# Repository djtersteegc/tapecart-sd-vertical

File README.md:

A respin of the [Tapuino](https://github.com/sweetlilmre/tapuino) hardware design for Kim Jorgensen's [Tapecart SD](https://github.com/KimJorgensen/tapecart) firmware that added SD support to Ingo Korb's original [Tapecart](https://github.com/ikorb/tapecart) project for the Commodore 64.  My three design goals for this were:

1. Full sized SD card slot.
2. Physically anchor the edge connector so insertion/removal forces don't stress the solder joints like some of the other designs.
3. SMD to make it as compact as possible, but keep the board single sided and using larger 0805 components with hand solder footprints to make it easy to build.

# Case

The case was created in DesignSpark and available in two different versions.  One with a finger pull handle for easy removal, and one without, but with grip ridges on the sides to aid in removal.  I find the Chinese Jamma/805 connectors from AliExpress to be extra tight on my Commodore's edge connectors, so the handle version is my preferred one.

There are a pair of light pipes that should be printed in transparent material, or you can just leave them off completely. The case is designed to be printed at 0.2mm layer heights and assembled with two M3x16mm screws through the connector body and two M3 nuts pushed into either the handle or lid.

# BOM

There's an interactive BOM [here](https://djtersteegc.github.io/tapecart-sd-vertical/ibom.html), and CSV version with footprint info [here](https://djtersteegc.github.io/tapecart-sd-vertical/bom.csv). The interactive one is super useful when placing the SMD comonents.

C5 is an optional bulk capacitor for the 5V power rail near the MCU.  In my experience building these it is not needed.

The LED's can either be driven directly from the ATmega328P, since they are only drawing ~10ma through the 330R resistors at R4 and R5, by bridging JP1 and JP2. You can also populate R2, R3, Q1, Q2 (leave JP1/2 open in this case) and drive them via a transistor like the original Tapuino design.

The SD card connector is commonly available from several different Chinese suppliers and often called "long body", "non popping", or "push pull" on AliExpress or eBay.

https://www.aliexpress.us/item/3256805779248826.html

Here's some links on LCSC.

https://www.lcsc.com/product-detail/SD-Card-Connectors_Hanbo-Electronic-SD-112_C961673.html

https://www.lcsc.com/product-detail/SD-Card-Connectors_XUNPU-SD-102_C266602.html

https://www.lcsc.com/product-detail/SD-Card-Connectors_Megastar-ZX-SD-282-8Y_C7419835.html

It should also cross with a Wurth 693063010911 or AMP GSD090012SEU if you want something domestically.

# Assembly

Assemble all the SMD components.  I use solder paste hand applied with pnematic dispenser and then finish on a hot plate.  But you can also hand solder, use hot air, or even order a stencil for paste application and use a proper reflow oven. I use a green LED for Read and Red for Write. Make sure to observe polarity with the green stripe on the LED to the right matching the white stripe on the PCB silkscreen.

Do NOT install the 2x3 ICSP pin header at J2.  I would recommend flashing the firmware at this point to do basic checks since it's easier to do board rework before you install the 805 connector.

To install the connector, you will want to print the case back first so it can be used a spacer between the connector and board.  Tighten the screws gently so you can still slide out the case in the future and then solder a couple pins to hold it.  Then slide out the case and do the rest.

When complete it should look something like this.

Press the light pipes into the two LED openings with the lip side facing up and then slide the board in. If you can't slide the PCB under the light pipes, they are installed upside down.  The side mounted LED's should keep the light pipes from falling out, even if they aren't a tight friction fit in the openings.

# Firmware Flashing

The ATmega328P is the same used an Arduino Uno/Nano/Micro, but lacks the necessary bootloader firmware and serial interfaces to flash via the Arduino IDE or programs like XLoader. You could program the chip before installing it with something like a [TL866/T48](TL866/T48) and a [TQFP32 to DIP 32 adapter](https://www.aliexpress.us/item/2251832227450089.html), but I prefer to just use a cheap [UBSASP](https://www.aliexpress.us/item/2251832600419163.html) and [avrdude](https://github.com/avrdudes/avrdude). Make sure you get a 10 pin to 8 pin adapter with the USBASP if it isn't natively an 8 pin model.

Since you didn't solder the 2x3 pin header on the ICSP port J2, you will need to hold the header pins at an angle in the holes to make contact while you run avrdude.  If you're feeling fancy, you could spring for a [2x3 double row 2.54mm test clip](https://www.aliexpress.us/item/3256805646654844.html) or [handheld pogo pin probe](https://www.aliexpress.us/item/3256805545980544.html).  The cheap angle method works fine for me.

The latest Tapecart SD firmware can be downloaded from Kim's repo, https://github.com/KimJorgensen/tapecart/releases

You will be burning the **tapecart.hex** file onto the board and placing the **browser.prg** C64 program on the root of the SD card.

In my [firmware](firmware) directory there are couple of Windows scripts and a test program to ensure your hardware is in good shape before you flash tapecart.hex and connect to your Commodore.

First you to need to setup your ATMega328p with the correct fuse setting so it uses the external 16 MHz crystal, same as an Arduino board. **burn-328p-fuses.cmd** executes the following:

`avrdude -c usbasp -p m328p -B 125kHz -U lfuse:w:0xFF:m -U hfuse:w:0xDE:m -U efuse:w:0x05:m`

Next I have a little test program that will verify the MCU, SD card, and LED's are all correctly wired and working.  **flash-tapecart-sd-test.cmd** will execute:

`avrdude -c usbasp -p m328p -u -U flash:w:tapecart-sd-test.ino.with_bootloader.standard.hex`

If everything is good, you should see the read and write LED's blink together in a loop.  If unable to open the SD card, the write (red) LED will light.  If the SD card is seen but browser.prg cannot be opened, then the read (green) LED will light.  If you don't see any LED's, something is wrong with either the ATMega328p, crystal, or LED wiring.

After everything checks out you can finally flash tapecart.hex with **flash-tapecart.cmd** that executes:

`avrdude -c usbasp -p m328p -u -U flash:w:tapecart.hex`

Plug into your Commodore and enjoy!  The browser program should load with either a **LOAD** command or pressing **SHIFT + RUN  STOP**.

# Getting a Board

If you are in the US, PCB's are available from my Tindie store, [https://www.tindie.com/products/tersteeg/commodore-tapecart-sd-pcb](https://www.tindie.com/products/tersteeg/commodore-tapecart-sd-pcb)

Otherwise you can grab the [gerbers](gerbers) and order from your favorite PCB fab.

# PCB Revisions

### Version 1.0

Q1 and Q2 footprints were incorrectly mapped to the schematic pins.  Could be made to work by wiring bodges directly to the LED current limiting resistors.

### Versions 1.1 (Current)

Fixed Q1/Q2 footprint to schematic mapping.  Added JP1 and JP2 to bypass resistors/transistors for direct operation of LED's from MCU outputs. No known issues.

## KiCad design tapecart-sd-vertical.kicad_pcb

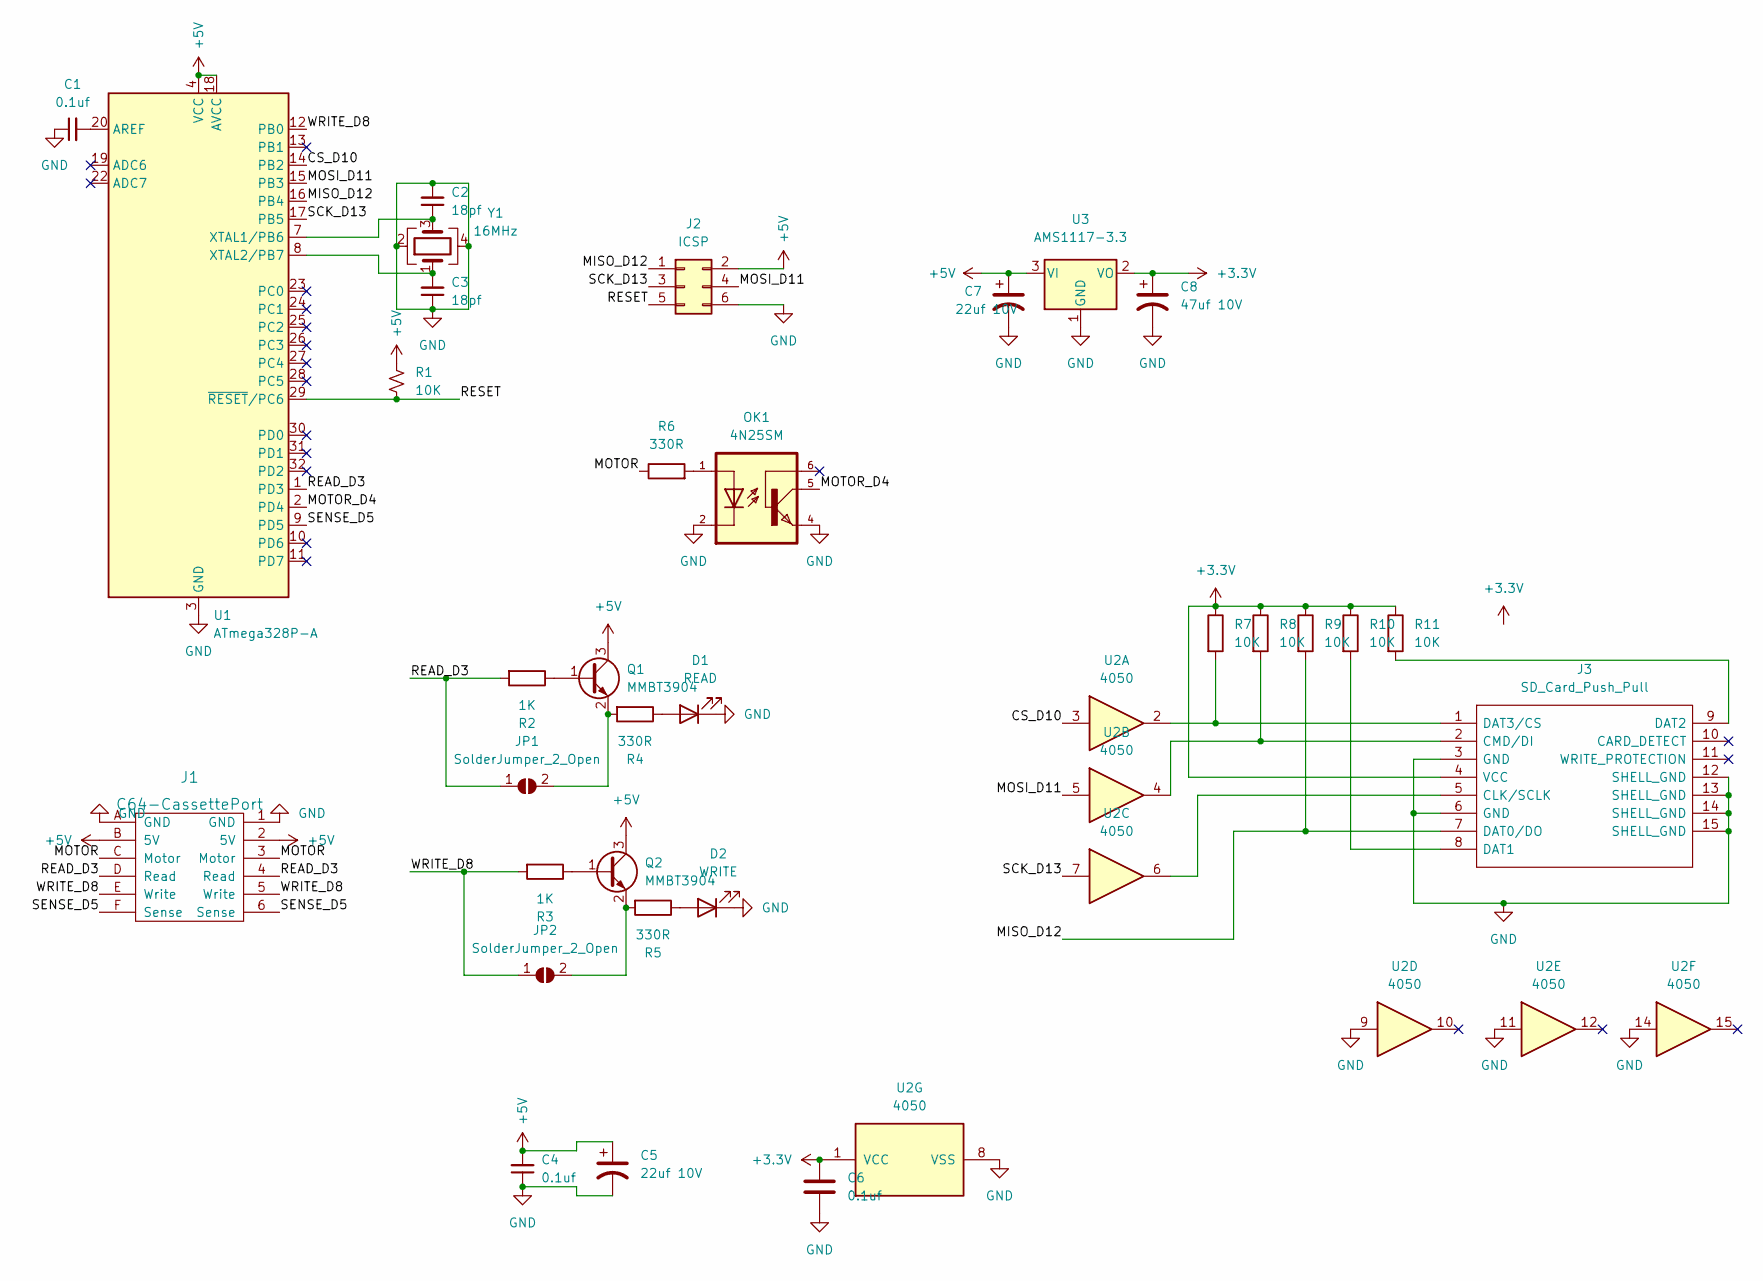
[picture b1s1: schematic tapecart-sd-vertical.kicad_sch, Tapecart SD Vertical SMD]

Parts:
C1, C4, C6: 0.1uf; C_0805_2012Metric_Pad1.18x1.45mm_HandSolder
C2, C3: 18pf; C_0805_2012Metric_Pad1.18x1.45mm_HandSolder
C5, C7: 22uf 10V; CP_EIA-3216-18_Kemet-A_Pad1.58x1.35mm_HandSolder
C8: 47uf 10V; CP_EIA-3528-12_Kemet-T_Pad1.50x2.35mm_HandSolder
D1: READ; 1204 Side Emitting LED
D2: WRITE; 1204 Side Emitting LED
J1: C64-CassettePort; JAMMA_Dark_Blue_2x06_P3.96mm_Horizontal_44.8mm_Wide
J2: ICSP; IDC-Header_2x03_P2.54mm_Vertical
J3: SD_Card_Push_Pull; 2041021-3_2; Manufacturer_Part_Number 2041021-3; Mouser Part Number 571-2041021-3
JP1, JP2: SolderJumper_2_Open; SolderJumper-2_P1.3mm_Open_TrianglePad1.0x1.5mm
OK1: 4N25SM; DIL6-SMD
Q1, Q2: MMBT3904; SOT-23
R1, R7, R8, R9, R10, R11: 10K; R_0805_2012Metric_Pad1.20x1.40mm_HandSolder
R2, R3: 1K; R_0805_2012Metric_Pad1.20x1.40mm_HandSolder
R4, R5, R6: 330R; R_0805_2012Metric_Pad1.20x1.40mm_HandSolder
U1: ATmega328P-A; TQFP-32_7x7mm_P0.8mm
U2: 4050; SOIC-16_3.9x9.9mm_P1.27mm
U3: AMS1117-3.3; SOT-223-3_TabPin2
Y1: 16MHz; Crystal_SMD_3225-4Pin_3.2x2.5mm_HandSoldering

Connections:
+3.3V: C6.2, C8.1, J3.4 (VCC), R7.1, R8.1, R9.1, R10.1, R11.1, U2.1 (VCC), U3.2 (VO)
+5V: C4.2, C5.1, C7.1, J1.2 (5V), J1.B (5V), J2.2, Q1.3 (C), Q2.3 (C), R1.1, U1.4 (VCC), U1.6 (VCC), U1.18 (AVCC), U3.3 (VI)
/CS_D10: U1.14 (PB2), U2.3
/MISO_D12: J2.1, J3.7 (DAT0/DO), R9.2, U1.16 (PB4)
/MOSI_D11: J2.4, U1.15 (PB3), U2.5
/MOTOR: J1.3 (Motor), J1.C (Motor), R6.1
/MOTOR_D4: OK1.5, U1.2 (PD4)
/READ_D3: J1.4 (Read), J1.D (Read), JP1.1 (A), R2.2, U1.1 (PD3)
/RESET: J2.5, R1.2, U1.29 (~RESET/PC6)
/SCK_D13: J2.3, U1.17 (PB5), U2.7
/SENSE_D5: J1.6 (Sense), J1.F (Sense), U1.9 (PD5)
/WRITE_D8: J1.5 (Write), J1.E (Write), JP2.1 (A), R3.2, U1.12 (PB0)
GND: C1.1, C2.2, C3.1, C4.1, C5.2, C6.1, C7.2, C8.2, D1.1 (K), D2.1 (K), J1.1 (GND), J1.A (GND), J2.6, J3.3 (GND), J3.6 (GND), J3.12 (SHELL_GND), J3.13 (SHELL_GND), J3.14 (SHELL_GND), J3.15 (SHELL_GND), OK1.2, OK1.4, U1.3 (GND), U1.5 (GND), U1.21 (GND), U2.8 (VSS), U2.9, U2.11, U2.14, U3.1 (GND), Y1.2, Y1.4
unnamed: D1.2 (A), R4.1
unnamed: D2.2 (A), R5.1
unnamed: J3.5 (CLK/SCLK), U2.6
unnamed: J3.2 (CMD/DI), R8.2, U2.4
unnamed: J3.8 (DAT1), R10.2
unnamed: J3.9 (DAT2), R11.2
unnamed: J3.1 (DAT3/CS), R7.2, U2.2
unnamed: JP1.2 (B), Q1.2 (E), R4.2
unnamed: JP2.2 (B), Q2.2 (E), R5.2
unnamed: OK1.1, R6.2
unnamed: Q1.1 (B), R2.1
unnamed: Q2.1 (B), R3.1
unnamed: C1.2, U1.20 (AREF)
unnamed: C2.1, U1.7 (XTAL1/PB6), Y1.3
unnamed: C3.2, U1.8 (XTAL2/PB7), Y1.1

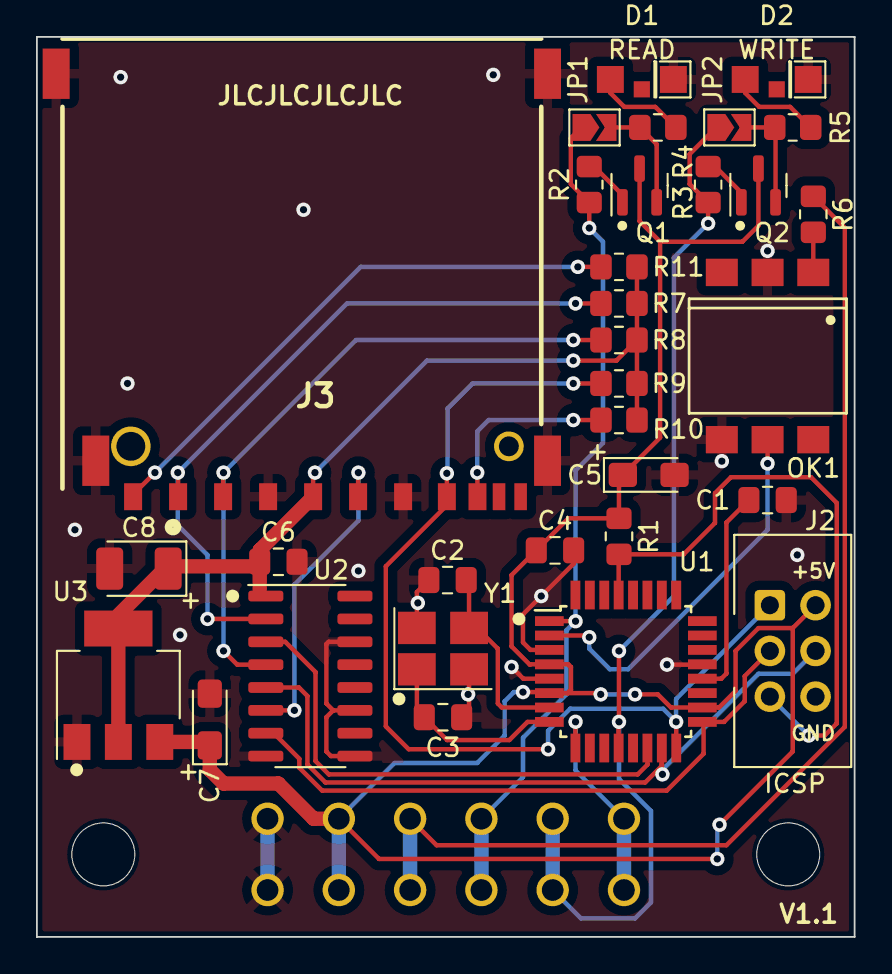
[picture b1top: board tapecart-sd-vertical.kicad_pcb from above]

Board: 2 copper layers, 45.4 x 50.0 mm, 33 parts (1 on the bottom side), 28 nets.

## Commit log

2023-12-24 Version 1.1
